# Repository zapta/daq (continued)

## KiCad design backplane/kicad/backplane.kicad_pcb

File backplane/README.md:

# Data Acquisition - Backplane

| :warning: WARNING                                               |
| :-------------------------------------------------------------- |
| This design is an unverified work in progress (as of May 2023). |

## Overview

The backplane is is a passive motherboard that accepts plugin boards with the functionality of the DAQ system.

## Design decisions

* Passive design, all active components are on plugin boards.
* Using common and inexpensive PCIE X8 connectors (98 pins). However, the power and signals are not compatible with PCIE.
* Symmetric slots. Slots are interchangeable and boards can be plugged in any slot. When applicable, conflict resolution is delegated to the plugin boards, e.g. using configuration jumpers.
* Scalable. Versions with higher/lower number of slots can be easily derived.
* 12-24VDC Power is provided via an on board connector and is routed to all slots. Plugin boards should use **insulated** DC/DC converters to generate supply rail voltages.
* Assigned pins for 5V supply, which is provided by an insulated power supply plugin board.
* Using through hole connectors for mechanical rigidity. An SMD version can be derived if so desired.
* 'Sufficient' signal integrity and bandwidth. The backplane is intended for relatively slow signals at the order of 1Mhz, that are driven directly by an MCU and peripherals, and thus, the backplane uses an inexpensive 4 layers PCB and minimal number of GND pins.

## Mechanical Dimensions

140mm X 67mm, 4 layers.

## Signals Assignment

As of May 2023, these are the assigned bus pins. All are reserved.

> **_TODO:_** Add the rest of the signals.

| Pin | Signal | Notes                            | Pin | Signal | Notes               |
| --- | ------ | -------------------------------- | --- | ------ | ------------------- |
| B1  | +5V    | Generated by Power Supply board. | A1  | GND    |                     |
| B2  | +5V    | Generated by Power Supply board. | A2  | GND    |                     |
| B3  | +5V    | Generated by Power Supply board. | A3  | GND    |                     |
| B4  | +5V    | Generated by Power Supply board. | A4  | GND    |                     |
| ... |        |                                  |     |        |                     |
| B48 | VIN+   | Insulated from GND. 12-24VDC     | A48 | VIN-   | Insulated from GND. |
| B49 | VIN+   | Insulated from GND. 12-24VDC     | A49 | VIN-   | Insulated from GND. |

## BOM

The key components are:

* PCIE X8 (98 pins) through hole connected. Preferably non slotted.
* JST XH two pin connector, preferably with positioning pin.

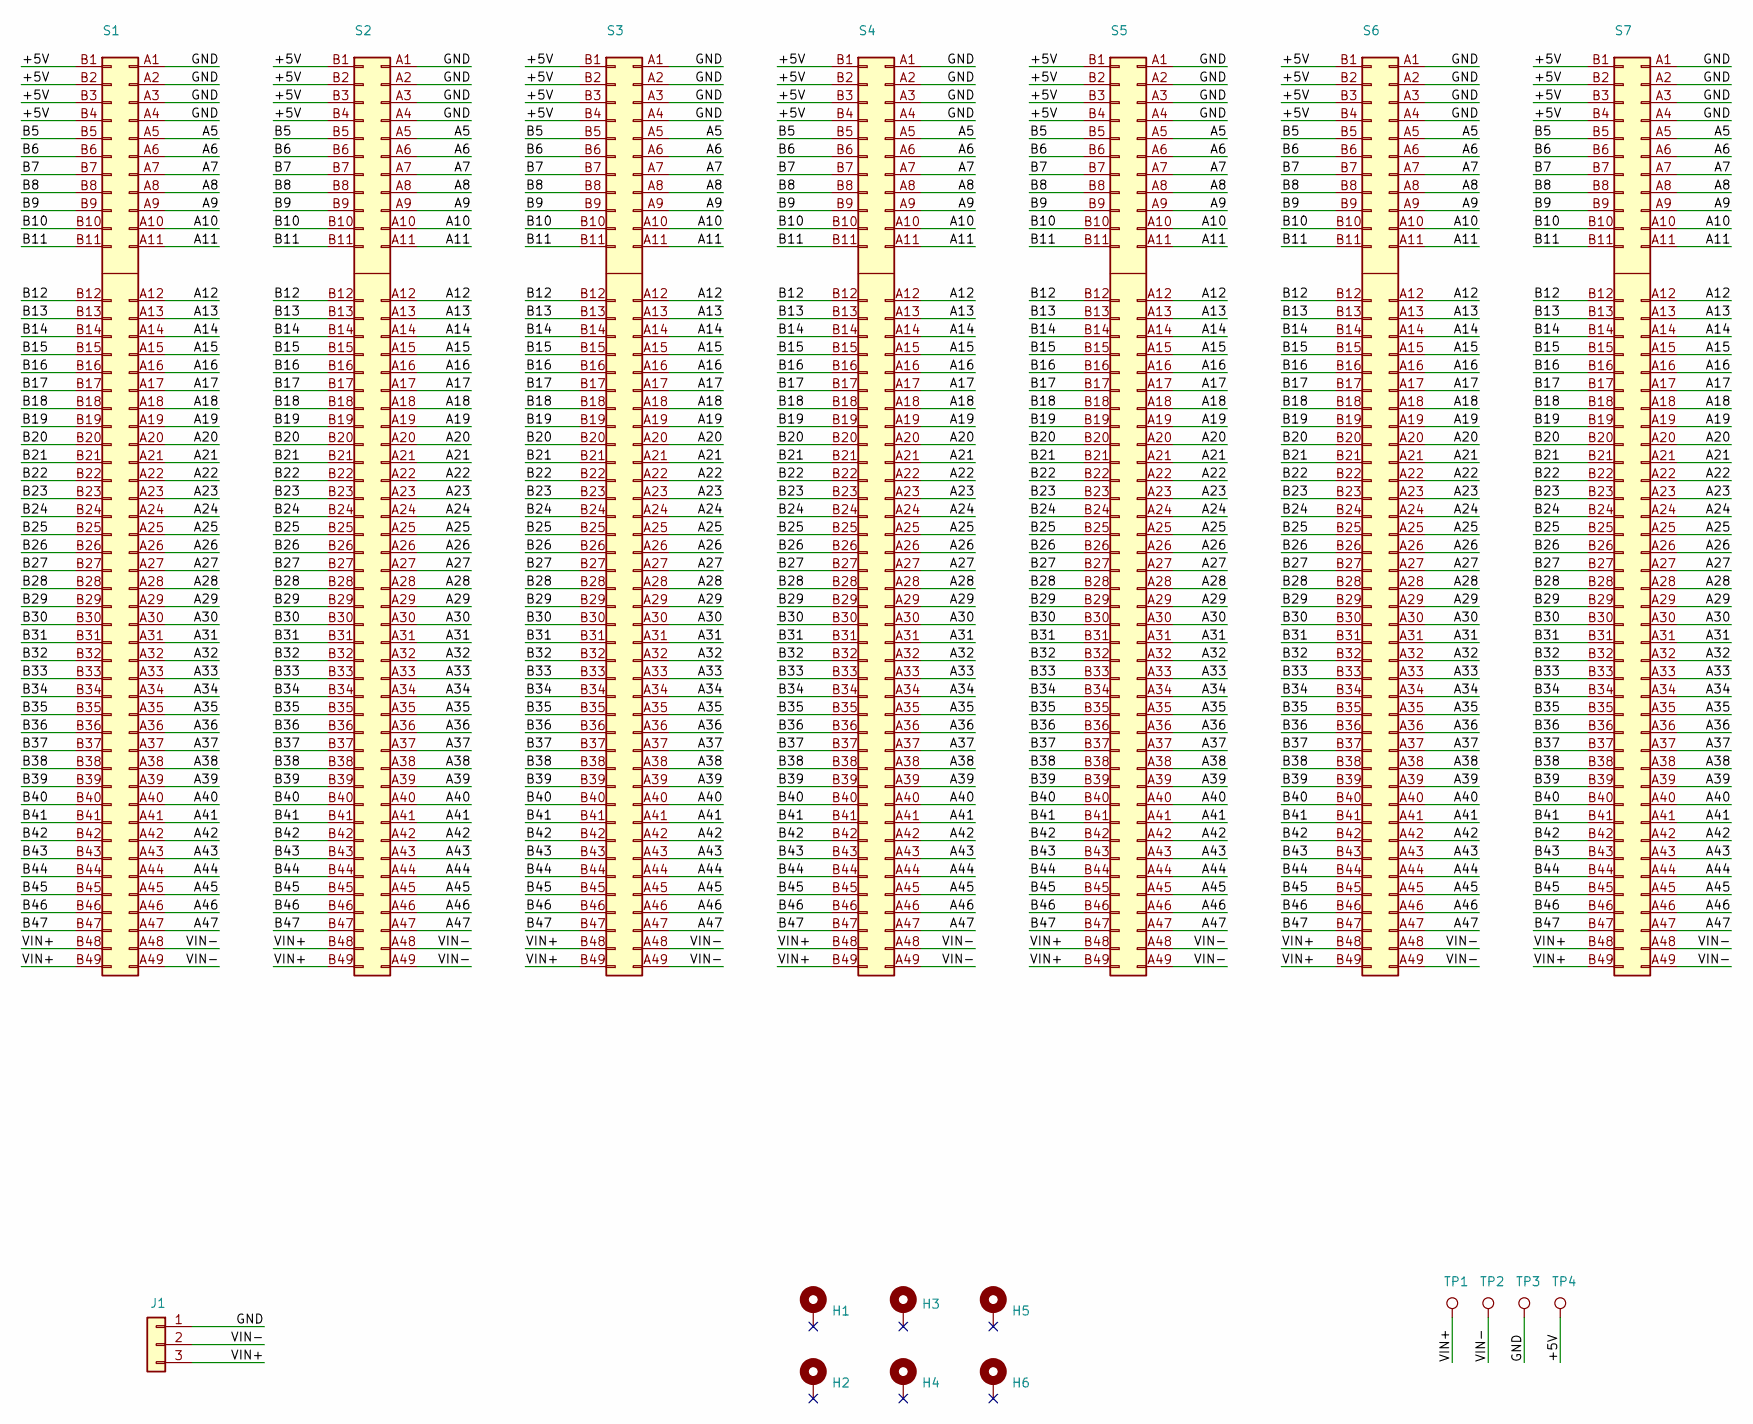
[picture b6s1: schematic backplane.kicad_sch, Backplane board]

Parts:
H1, H2, H3, H4, H5, H6: MountingHole; MountingHole_3.2mm_M3_Pad_Via
J1: Conn_01x02_Pin; TerminalBlock_3P_7.62mm; LCSC C557662
S1, S2, S3, S4, S5, S6, S7: pcie_98; pcie_98_socket
TP1, TP2, TP3, TP4: TestPoint; Test_Pad

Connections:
/+5V: S1.B1 (Pin_b1), S1.B2 (Pin_b2), S1.B3 (Pin_b3), S1.B4 (Pin_b4), S2.B1 (Pin_b1), S2.B2 (Pin_b2), S2.B3 (Pin_b3), S2.B4 (Pin_b4), S3.B1 (Pin_b1), S3.B2 (Pin_b2), S3.B3 (Pin_b3), S3.B4 (Pin_b4), S4.B1 (Pin_b1), S4.B2 (Pin_b2), S4.B3 (Pin_b3), S4.B4 (Pin_b4), S5.B1 (Pin_b1), S5.B2 (Pin_b2), S5.B3 (Pin_b3), S5.B4 (Pin_b4), S6.B1 (Pin_b1), S6.B2 (Pin_b2), S6.B3 (Pin_b3), S6.B4 (Pin_b4), S7.B1 (Pin_b1), S7.B2 (Pin_b2), S7.B3 (Pin_b3), S7.B4 (Pin_b4), TP4.1
/A5: S1.A5 (Pin_a5), S2.A5 (Pin_a5), S3.A5 (Pin_a5), S4.A5 (Pin_a5), S5.A5 (Pin_a5), S6.A5 (Pin_a5), S7.A5 (Pin_a5)
/A6: S1.A6 (Pin_a6), S2.A6 (Pin_a6), S3.A6 (Pin_a6), S4.A6 (Pin_a6), S5.A6 (Pin_a6), S6.A6 (Pin_a6), S7.A6 (Pin_a6)
/A7: S1.A7 (Pin_a7), S2.A7 (Pin_a7), S3.A7 (Pin_a7), S4.A7 (Pin_a7), S5.A7 (Pin_a7), S6.A7 (Pin_a7), S7.A7 (Pin_a7)
/A8: S1.A8 (Pin_a8), S2.A8 (Pin_a8), S3.A8 (Pin_a8), S4.A8 (Pin_a8), S5.A8 (Pin_a8), S6.A8 (Pin_a8), S7.A8 (Pin_a8)
/A9: S1.A9 (Pin_a9), S2.A9 (Pin_a9), S3.A9 (Pin_a9), S4.A9 (Pin_a9), S5.A9 (Pin_a9), S6.A9 (Pin_a9), S7.A9 (Pin_a9)
/A10: S1.A10 (Pin_a10), S2.A10 (Pin_a10), S3.A10 (Pin_a10), S4.A10 (Pin_a10), S5.A10 (Pin_a10), S6.A10 (Pin_a10), S7.A10 (Pin_a10)
/A11: S1.A11, S2.A11, S3.A11, S4.A11, S5.A11, S6.A11, S7.A11
/A12: S1.A12 (Pin_a12), S2.A12 (Pin_a12), S3.A12 (Pin_a12), S4.A12 (Pin_a12), S5.A12 (Pin_a12), S6.A12 (Pin_a12), S7.A12 (Pin_a12)
/A13: S1.A13 (Pin_a13), S2.A13 (Pin_a13), S3.A13 (Pin_a13), S4.A13 (Pin_a13), S5.A13 (Pin_a13), S6.A13 (Pin_a13), S7.A13 (Pin_a13)
/A14: S1.A14 (Pin_a14), S2.A14 (Pin_a14), S3.A14 (Pin_a14), S4.A14 (Pin_a14), S5.A14 (Pin_a14), S6.A14 (Pin_a14), S7.A14 (Pin_a14)
/A15: S1.A15 (Pin_a15), S2.A15 (Pin_a15), S3.A15 (Pin_a15), S4.A15 (Pin_a15), S5.A15 (Pin_a15), S6.A15 (Pin_a15), S7.A15 (Pin_a15)
/A16: S1.A16 (Pin_a16), S2.A16 (Pin_a16), S3.A16 (Pin_a16), S4.A16 (Pin_a16), S5.A16 (Pin_a16), S6.A16 (Pin_a16), S7.A16 (Pin_a16)
/A17: S1.A17 (Pin_a17), S2.A17 (Pin_a17), S3.A17 (Pin_a17), S4.A17 (Pin_a17), S5.A17 (Pin_a17), S6.A17 (Pin_a17), S7.A17 (Pin_a17)
/A18: S1.A18 (Pin_a18), S2.A18 (Pin_a18), S3.A18 (Pin_a18), S4.A18 (Pin_a18), S5.A18 (Pin_a18), S6.A18 (Pin_a18), S7.A18 (Pin_a18)
/A19: S1.A19 (Pin_a19), S2.A19 (Pin_a19), S3.A19 (Pin_a19), S4.A19 (Pin_a19), S5.A19 (Pin_a19), S6.A19 (Pin_a19), S7.A19 (Pin_a19)
/A20: S1.A20 (Pin_a20), S2.A20 (Pin_a20), S3.A20 (Pin_a20), S4.A20 (Pin_a20), S5.A20 (Pin_a20), S6.A20 (Pin_a20), S7.A20 (Pin_a20)
/A21: S1.A21 (Pin_a21), S2.A21 (Pin_a21), S3.A21 (Pin_a21), S4.A21 (Pin_a21), S5.A21 (Pin_a21), S6.A21 (Pin_a21), S7.A21 (Pin_a21)
/A22: S1.A22 (Pin_a22), S2.A22 (Pin_a22), S3.A22 (Pin_a22), S4.A22 (Pin_a22), S5.A22 (Pin_a22), S6.A22 (Pin_a22), S7.A22 (Pin_a22)
/A23: S1.A23 (Pin_a23), S2.A23 (Pin_a23), S3.A23 (Pin_a23), S4.A23 (Pin_a23), S5.A23 (Pin_a23), S6.A23 (Pin_a23), S7.A23 (Pin_a23)
/A24: S1.A24 (Pin_a24), S2.A24 (Pin_a24), S3.A24 (Pin_a24), S4.A24 (Pin_a24), S5.A24 (Pin_a24), S6.A24 (Pin_a24), S7.A24 (Pin_a24)
/A25: S1.A25 (Pin_a25), S2.A25 (Pin_a25), S3.A25 (Pin_a25), S4.A25 (Pin_a25), S5.A25 (Pin_a25), S6.A25 (Pin_a25), S7.A25 (Pin_a25)
/A26: S1.A26 (Pin_a26), S2.A26 (Pin_a26), S3.A26 (Pin_a26), S4.A26 (Pin_a26), S5.A26 (Pin_a26), S6.A26 (Pin_a26), S7.A26 (Pin_a26)
/A27: S1.A27 (Pin_a27), S2.A27 (Pin_a27), S3.A27 (Pin_a27), S4.A27 (Pin_a27), S5.A27 (Pin_a27), S6.A27 (Pin_a27), S7.A27 (Pin_a27)
/A28: S1.A28 (Pin_a28), S2.A28 (Pin_a28), S3.A28 (Pin_a28), S4.A28 (Pin_a28), S5.A28 (Pin_a28), S6.A28 (Pin_a28), S7.A28 (Pin_a28)
/A29: S1.A29 (Pin_a29), S2.A29 (Pin_a29), S3.A29 (Pin_a29), S4.A29 (Pin_a29), S5.A29 (Pin_a29), S6.A29 (Pin_a29), S7.A29 (Pin_a29)
/A30: S1.A30 (Pin_a30), S2.A30 (Pin_a30), S3.A30 (Pin_a30), S4.A30 (Pin_a30), S5.A30 (Pin_a30), S6.A30 (Pin_a30), S7.A30 (Pin_a30)
/A31: S1.A31 (Pin_a31), S2.A31 (Pin_a31), S3.A31 (Pin_a31), S4.A31 (Pin_a31), S5.A31 (Pin_a31), S6.A31 (Pin_a31), S7.A31 (Pin_a31)
/A32: S1.A32 (Pin_a32), S2.A32 (Pin_a32), S3.A32 (Pin_a32), S4.A32 (Pin_a32), S5.A32 (Pin_a32), S6.A32 (Pin_a32), S7.A32 (Pin_a32)
/A33: S1.A33 (Pin_a33), S2.A33 (Pin_a33), S3.A33 (Pin_a33), S4.A33 (Pin_a33), S5.A33 (Pin_a33), S6.A33 (Pin_a33), S7.A33 (Pin_a33)
/A34: S1.A34 (Pin_a34), S2.A34 (Pin_a34), S3.A34 (Pin_a34), S4.A34 (Pin_a34), S5.A34 (Pin_a34), S6.A34 (Pin_a34), S7.A34 (Pin_a34)
/A35: S1.A35 (Pin_a35), S2.A35 (Pin_a35), S3.A35 (Pin_a35), S4.A35 (Pin_a35), S5.A35 (Pin_a35), S6.A35 (Pin_a35), S7.A35 (Pin_a35)
/A36: S1.A36 (Pin_a36), S2.A36 (Pin_a36), S3.A36 (Pin_a36), S4.A36 (Pin_a36), S5.A36 (Pin_a36), S6.A36 (Pin_a36), S7.A36 (Pin_a36)
/A37: S1.A37 (Pin_a37), S2.A37 (Pin_a37), S3.A37 (Pin_a37), S4.A37 (Pin_a37), S5.A37 (Pin_a37), S6.A37 (Pin_a37), S7.A37 (Pin_a37)
/A38: S1.A38 (Pin_a38), S2.A38 (Pin_a38), S3.A38 (Pin_a38), S4.A38 (Pin_a38), S5.A38 (Pin_a38), S6.A38 (Pin_a38), S7.A38 (Pin_a38)
/A39: S1.A39 (Pin_a39), S2.A39 (Pin_a39), S3.A39 (Pin_a39), S4.A39 (Pin_a39), S5.A39 (Pin_a39), S6.A39 (Pin_a39), S7.A39 (Pin_a39)
/A40: S1.A40 (Pin_a40), S2.A40 (Pin_a40), S3.A40 (Pin_a40), S4.A40 (Pin_a40), S5.A40 (Pin_a40), S6.A40 (Pin_a40), S7.A40 (Pin_a40)
/A41: S1.A41 (Pin_a41), S2.A41 (Pin_a41), S3.A41 (Pin_a41), S4.A41 (Pin_a41), S5.A41 (Pin_a41), S6.A41 (Pin_a41), S7.A41 (Pin_a41)
/A42: S1.A42 (Pin_a42), S2.A42 (Pin_a42), S3.A42 (Pin_a42), S4.A42 (Pin_a42), S5.A42 (Pin_a42), S6.A42 (Pin_a42), S7.A42 (Pin_a42)
/A43: S1.A43 (Pin_a43), S2.A43 (Pin_a43), S3.A43 (Pin_a43), S4.A43 (Pin_a43), S5.A43 (Pin_a43), S6.A43 (Pin_a43), S7.A43 (Pin_a43)
/A44: S1.A44 (Pin_a44), S2.A44 (Pin_a44), S3.A44 (Pin_a44), S4.A44 (Pin_a44), S5.A44 (Pin_a44), S6.A44 (Pin_a44), S7.A44 (Pin_a44)
/A45: S1.A45 (Pin_a45), S2.A45 (Pin_a45), S3.A45 (Pin_a45), S4.A45 (Pin_a45), S5.A45 (Pin_a45), S6.A45 (Pin_a45), S7.A45 (Pin_a45)
/A46: S1.A46 (Pin_a46), S2.A46 (Pin_a46), S3.A46 (Pin_a46), S4.A46 (Pin_a46), S5.A46 (Pin_a46), S6.A46 (Pin_a46), S7.A46 (Pin_a46)
/A47: S1.A47 (Pin_a47), S2.A47 (Pin_a47), S3.A47 (Pin_a47), S4.A47 (Pin_a47), S5.A47 (Pin_a47), S6.A47 (Pin_a47), S7.A47 (Pin_a47)
/B5: S1.B5 (Pin_b5), S2.B5 (Pin_b5), S3.B5 (Pin_b5), S4.B5 (Pin_b5), S5.B5 (Pin_b5), S6.B5 (Pin_b5), S7.B5 (Pin_b5)
/B6: S1.B6 (Pin_b6), S2.B6 (Pin_b6), S3.B6 (Pin_b6), S4.B6 (Pin_b6), S5.B6 (Pin_b6), S6.B6 (Pin_b6), S7.B6 (Pin_b6)
/B7: S1.B7 (Pin_b7), S2.B7 (Pin_b7), S3.B7 (Pin_b7), S4.B7 (Pin_b7), S5.B7 (Pin_b7), S6.B7 (Pin_b7), S7.B7 (Pin_b7)
/B8: S1.B8 (Pin_b8), S2.B8 (Pin_b8), S3.B8 (Pin_b8), S4.B8 (Pin_b8), S5.B8 (Pin_b8), S6.B8 (Pin_b8), S7.B8 (Pin_b8)
/B9: S1.B9 (Pin_b9), S2.B9 (Pin_b9), S3.B9 (Pin_b9), S4.B9 (Pin_b9), S5.B9 (Pin_b9), S6.B9 (Pin_b9), S7.B9 (Pin_b9)
/B10: S1.B10 (Pin_b10), S2.B10 (Pin_b10), S3.B10 (Pin_b10), S4.B10 (Pin_b10), S5.B10 (Pin_b10), S6.B10 (Pin_b10), S7.B10 (Pin_b10)
/B11: S1.B11 (Pin_b11), S2.B11 (Pin_b11), S3.B11 (Pin_b11), S4.B11 (Pin_b11), S5.B11 (Pin_b11), S6.B11 (Pin_b11), S7.B11 (Pin_b11)
/B12: S1.B12 (Pin_b12), S2.B12 (Pin_b12), S3.B12 (Pin_b12), S4.B12 (Pin_b12), S5.B12 (Pin_b12), S6.B12 (Pin_b12), S7.B12 (Pin_b12)
/B13: S1.B13 (Pin_b13), S2.B13 (Pin_b13), S3.B13 (Pin_b13), S4.B13 (Pin_b13), S5.B13 (Pin_b13), S6.B13 (Pin_b13), S7.B13 (Pin_b13)
/B14: S1.B14 (Pin_b14), S2.B14 (Pin_b14), S3.B14 (Pin_b14), S4.B14 (Pin_b14), S5.B14 (Pin_b14), S6.B14 (Pin_b14), S7.B14 (Pin_b14)
/B15: S1.B15 (Pin_b15), S2.B15 (Pin_b15), S3.B15 (Pin_b15), S4.B15 (Pin_b15), S5.B15 (Pin_b15), S6.B15 (Pin_b15), S7.B15 (Pin_b15)
/B16: S1.B16 (Pin_b16), S2.B16 (Pin_b16), S3.B16 (Pin_b16), S4.B16 (Pin_b16), S5.B16 (Pin_b16), S6.B16 (Pin_b16), S7.B16 (Pin_b16)
/B17: S1.B17 (Pin_b17), S2.B17 (Pin_b17), S3.B17 (Pin_b17), S4.B17 (Pin_b17), S5.B17 (Pin_b17), S6.B17 (Pin_b17), S7.B17 (Pin_b17)
/B18: S1.B18 (Pin_b18), S2.B18 (Pin_b18), S3.B18 (Pin_b18), S4.B18 (Pin_b18), S5.B18 (Pin_b18), S6.B18 (Pin_b18), S7.B18 (Pin_b18)
/B19: S1.B19 (Pin_b19), S2.B19 (Pin_b19), S3.B19 (Pin_b19), S4.B19 (Pin_b19), S5.B19 (Pin_b19), S6.B19 (Pin_b19), S7.B19 (Pin_b19)
/B20: S1.B20 (Pin_b20), S2.B20 (Pin_b20), S3.B20 (Pin_b20), S4.B20 (Pin_b20), S5.B20 (Pin_b20), S6.B20 (Pin_b20), S7.B20 (Pin_b20)
/B21: S1.B21 (Pin_b21), S2.B21 (Pin_b21), S3.B21 (Pin_b21), S4.B21 (Pin_b21), S5.B21 (Pin_b21), S6.B21 (Pin_b21), S7.B21 (Pin_b21)
/B22: S1.B22 (Pin_b22), S2.B22 (Pin_b22), S3.B22 (Pin_b22), S4.B22 (Pin_b22), S5.B22 (Pin_b22), S6.B22 (Pin_b22), S7.B22 (Pin_b22)
/B23: S1.B23 (Pin_b23), S2.B23 (Pin_b23), S3.B23 (Pin_b23), S4.B23 (Pin_b23), S5.B23 (Pin_b23), S6.B23 (Pin_b23), S7.B23 (Pin_b23)
/B24: S1.B24 (Pin_b24), S2.B24 (Pin_b24), S3.B24 (Pin_b24), S4.B24 (Pin_b24), S5.B24 (Pin_b24), S6.B24 (Pin_b24), S7.B24 (Pin_b24)
/B25: S1.B25 (Pin_b25), S2.B25 (Pin_b25), S3.B25 (Pin_b25), S4.B25 (Pin_b25), S5.B25 (Pin_b25), S6.B25 (Pin_b25), S7.B25 (Pin_b25)
/B26: S1.B26 (Pin_b26), S2.B26 (Pin_b26), S3.B26 (Pin_b26), S4.B26 (Pin_b26), S5.B26 (Pin_b26), S6.B26 (Pin_b26), S7.B26 (Pin_b26)
/B27: S1.B27 (Pin_b27), S2.B27 (Pin_b27), S3.B27 (Pin_b27), S4.B27 (Pin_b27), S5.B27 (Pin_b27), S6.B27 (Pin_b27), S7.B27 (Pin_b27)
/B28: S1.B28 (Pin_b28), S2.B28 (Pin_b28), S3.B28 (Pin_b28), S4.B28 (Pin_b28), S5.B28 (Pin_b28), S6.B28 (Pin_b28), S7.B28 (Pin_b28)
/B29: S1.B29 (Pin_b29), S2.B29 (Pin_b29), S3.B29 (Pin_b29), S4.B29 (Pin_b29), S5.B29 (Pin_b29), S6.B29 (Pin_b29), S7.B29 (Pin_b29)
/B30: S1.B30 (Pin_b30), S2.B30 (Pin_b30), S3.B30 (Pin_b30), S4.B30 (Pin_b30), S5.B30 (Pin_b30), S6.B30 (Pin_b30), S7.B30 (Pin_b30)
/B31: S1.B31 (Pin_b31), S2.B31 (Pin_b31), S3.B31 (Pin_b31), S4.B31 (Pin_b31), S5.B31 (Pin_b31), S6.B31 (Pin_b31), S7.B31 (Pin_b31)
/B32: S1.B32 (Pin_b32), S2.B32 (Pin_b32), S3.B32 (Pin_b32), S4.B32 (Pin_b32), S5.B32 (Pin_b32), S6.B32 (Pin_b32), S7.B32 (Pin_b32)
/B33: S1.B33 (Pin_b33), S2.B33 (Pin_b33), S3.B33 (Pin_b33), S4.B33 (Pin_b33), S5.B33 (Pin_b33), S6.B33 (Pin_b33), S7.B33 (Pin_b33)
/B34: S1.B34 (Pin_b34), S2.B34 (Pin_b34), S3.B34 (Pin_b34), S4.B34 (Pin_b34), S5.B34 (Pin_b34), S6.B34 (Pin_b34), S7.B34 (Pin_b34)
/B35: S1.B35 (Pin_b35), S2.B35 (Pin_b35), S3.B35 (Pin_b35), S4.B35 (Pin_b35), S5.B35 (Pin_b35), S6.B35 (Pin_b35), S7.B35 (Pin_b35)
/B36: S1.B36 (Pin_b36), S2.B36 (Pin_b36), S3.B36 (Pin_b36), S4.B36 (Pin_b36), S5.B36 (Pin_b36), S6.B36 (Pin_b36), S7.B36 (Pin_b36)
/B37: S1.B37 (Pin_b37), S2.B37 (Pin_b37), S3.B37 (Pin_b37), S4.B37 (Pin_b37), S5.B37 (Pin_b37), S6.B37 (Pin_b37), S7.B37 (Pin_b37)
/B38: S1.B38 (Pin_b38), S2.B38 (Pin_b38), S3.B38 (Pin_b38), S4.B38 (Pin_b38), S5.B38 (Pin_b38), S6.B38 (Pin_b38), S7.B38 (Pin_b38)
/B39: S1.B39 (Pin_b39), S2.B39 (Pin_b39), S3.B39 (Pin_b39), S4.B39 (Pin_b39), S5.B39 (Pin_b39), S6.B39 (Pin_b39), S7.B39 (Pin_b39)
/B40: S1.B40 (Pin_b40), S2.B40 (Pin_b40), S3.B40 (Pin_b40), S4.B40 (Pin_b40), S5.B40 (Pin_b40), S6.B40 (Pin_b40), S7.B40 (Pin_b40)
/B41: S1.B41 (Pin_b41), S2.B41 (Pin_b41), S3.B41 (Pin_b41), S4.B41 (Pin_b41), S5.B41 (Pin_b41), S6.B41 (Pin_b41), S7.B41 (Pin_b41)
/B42: S1.B42 (Pin_b42), S2.B42 (Pin_b42), S3.B42 (Pin_b42), S4.B42 (Pin_b42), S5.B42 (Pin_b42), S6.B42 (Pin_b42), S7.B42 (Pin_b42)
/B43: S1.B43 (Pin_b43), S2.B43 (Pin_b43), S3.B43 (Pin_b43), S4.B43 (Pin_b43), S5.B43 (Pin_b43), S6.B43 (Pin_b43), S7.B43 (Pin_b43)
/B44: S1.B44 (Pin_b44), S2.B44 (Pin_b44), S3.B44 (Pin_b44), S4.B44 (Pin_b44), S5.B44 (Pin_b44), S6.B44 (Pin_b44), S7.B44 (Pin_b44)
/B45: S1.B45 (Pin_b45), S2.B45 (Pin_b45), S3.B45 (Pin_b45), S4.B45 (Pin_b45), S5.B45 (Pin_b45), S6.B45 (Pin_b45), S7.B45 (Pin_b45)
/B46: S1.B46 (Pin_46), S2.B46 (Pin_46), S3.B46 (Pin_46), S4.B46 (Pin_46), S5.B46 (Pin_46), S6.B46 (Pin_46), S7.B46 (Pin_46)
/B47: S1.B47 (Pin_b47), S2.B47 (Pin_b47), S3.B47 (Pin_b47), S4.B47 (Pin_b47), S5.B47 (Pin_b47), S6.B47 (Pin_b47), S7.B47 (Pin_b47)
/GND: J1.1, S1.A1 (Pin_a1), S1.A2 (Pin_a2), S1.A3 (Pin_a3), S1.A4 (Pin_a4), S2.A1 (Pin_a1), S2.A2 (Pin_a2), S2.A3 (Pin_a3), S2.A4 (Pin_a4), S3.A1 (Pin_a1), S3.A2 (Pin_a2), S3.A3 (Pin_a3), S3.A4 (Pin_a4), S4.A1 (Pin_a1), S4.A2 (Pin_a2), S4.A3 (Pin_a3), S4.A4 (Pin_a4), S5.A1 (Pin_a1), S5.A2 (Pin_a2), S5.A3 (Pin_a3), S5.A4 (Pin_a4), S6.A1 (Pin_a1), S6.A2 (Pin_a2), S6.A3 (Pin_a3), S6.A4 (Pin_a4), S7.A1 (Pin_a1), S7.A2 (Pin_a2), S7.A3 (Pin_a3), S7.A4 (Pin_a4), TP3.1
/VIN+: J1.3, S1.B48 (Pin_b48), S1.B49 (Pin_b49), S2.B48 (Pin_b48), S2.B49 (Pin_b49), S3.B48 (Pin_b48), S3.B49 (Pin_b49), S4.B48 (Pin_b48), S4.B49 (Pin_b49), S5.B48 (Pin_b48), S5.B49 (Pin_b49), S6.B48 (Pin_b48), S6.B49 (Pin_b49), S7.B48 (Pin_b48), S7.B49 (Pin_b49), TP1.1
/VIN-: J1.2, S1.A48 (Pin_a48), S1.A49 (Pin_a49), S2.A48 (Pin_a48), S2.A49 (Pin_a49), S3.A48 (Pin_a48), S3.A49 (Pin_a49), S4.A48 (Pin_a48), S4.A49 (Pin_a49), S5.A48 (Pin_a48), S5.A49 (Pin_a49), S6.A48 (Pin_a48), S6.A49 (Pin_a49), S7.A48 (Pin_a48), S7.A49 (Pin_a49), TP2.1

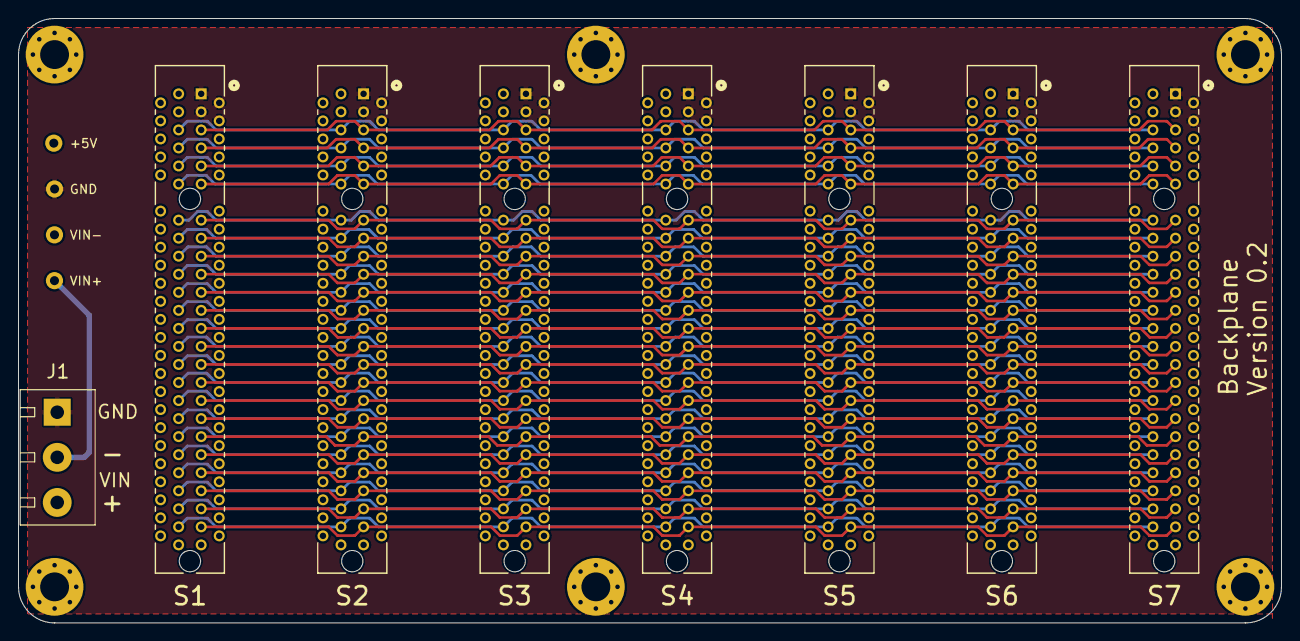
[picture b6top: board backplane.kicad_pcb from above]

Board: 4 copper layers, 140.0 x 67.0 mm, 18 parts (0 on the bottom side), 90 nets.

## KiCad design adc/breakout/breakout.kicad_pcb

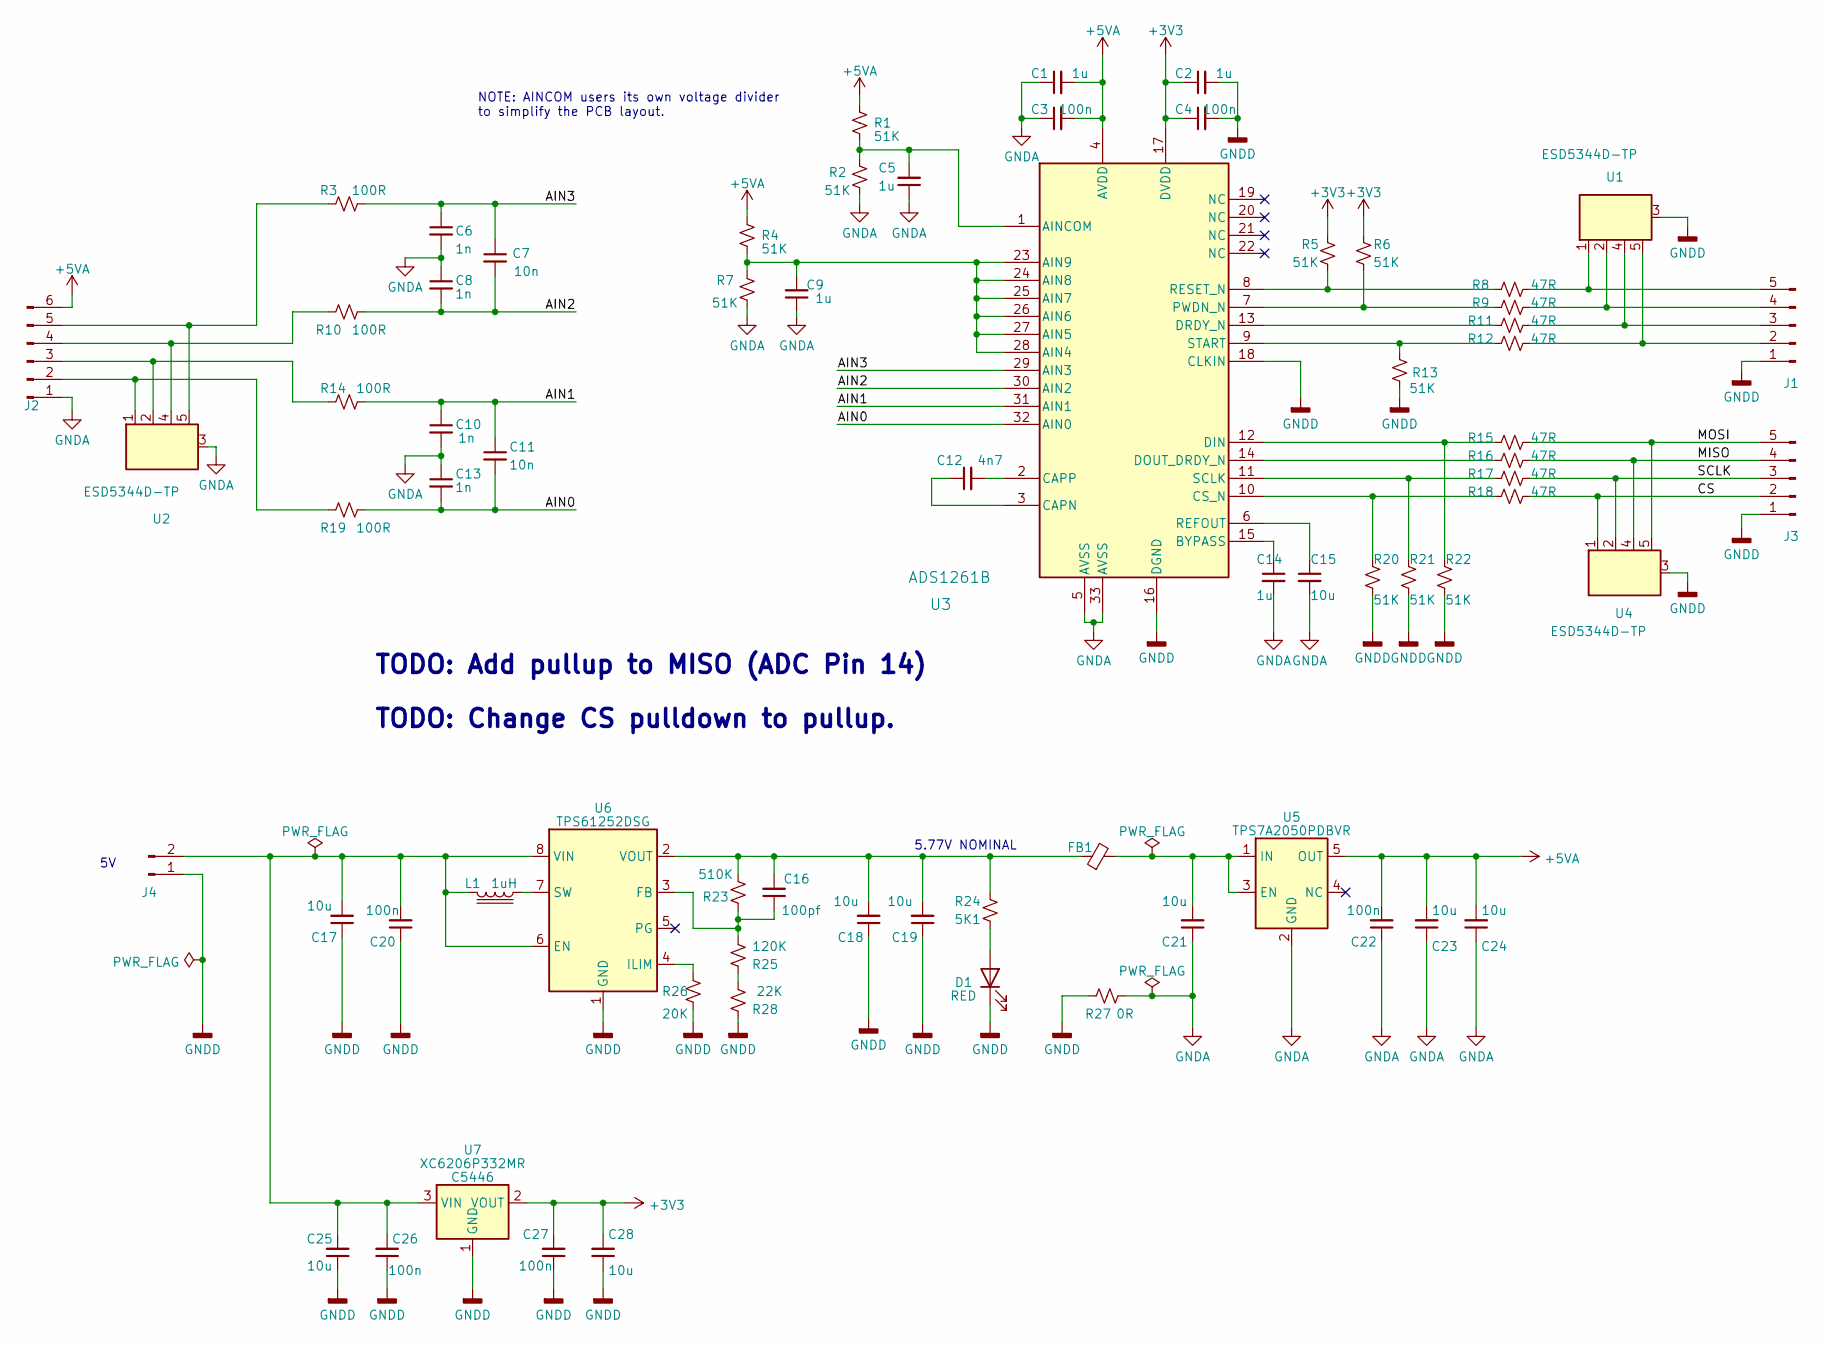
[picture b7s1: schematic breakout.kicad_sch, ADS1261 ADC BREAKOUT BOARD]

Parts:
C1, C2, C5, C9, C14: 1u; C_0402_1005Metric; LCSC C52923
C3, C4, C20, C22, C26, C27: 100n; C_0402_1005Metric; LCSC C1525
C6, C8, C10, C13: 1n; C_0402_1005Metric; LCSC C1523
C7, C11: 10n; C_0402_1005Metric; LCSC C15195
C12: 4n7; C_0402_1005Metric; LCSC C1538
C15, C17, C18, C19, C21, C23, C24, C25, C28: 10u; C_0603_1608Metric; LCSC C96446
C16: 100pf; C_0402_1005Metric; LCSC C1546
D1: RED; LED_0805_2012Metric; LCSC C84256
FB1: Ferrite Bead; L_0805_2012Metric; LCSC C1017
J1, J3: Conn_01x05_Pin; PinHeader_1x05_P2.54mm_Vertical; LCSC DNP
J2: Conn_01x06_Pin; PinHeader_1x06_P2.54mm_Vertical; LCSC DNP
J4: Conn_01x03_Pin; PinHeader_1x02_P2.54mm_Vertical; LCSC DNP
L1: 1uH; L_1210_3225Metric; LCSC C703782
R1, R2, R4, R5, R6, R7, R13, R20, R21, R22: 51K; R_0402_1005Metric; LCSC C25794
R3, R10, R14, R19: 100R; R_0402_1005Metric; LCSC C25076
R8, R9, R11, R12, R15, R16, R17, R18: 47R; R_0402_1005Metric; LCSC C25118
R23: 510K; R_0402_1005Metric; LCSC C11616
R24: 5K1; R_0402_1005Metric; LCSC C25905
R25: 120K; R_0402_1005Metric; LCSC C25750
R26: 20K; R_0402_1005Metric; LCSC C25765
R27: 0R; R_0805_2012Metric; LCSC C17477
R28: 22K; R_0402_1005Metric; LCSC C25768
U1, U2, U4: ESD5344D-TP; Diodes_UDFN-10_1.0x2.5mm_P0.5mm; LCSC C2841840
U3: ADS1261B; RHB0032E; LCSC DNP
U5: TPS7A2050PDBVR; SOT-23-5; LCSC DNP
U6: TPS61252DSG; WSON-8-1EP_2x2mm_P0.5mm_EP0.9x1.6mm; LCSC C128617
U7: XC6206P332MR; SOT-23-3; LCSC C5446

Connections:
+3V3: C2.1, C4.1, C27.2, C28.2, R5.2, R6.2, U3.17 (DVDD), U7.2 (VOUT)
+5VA: C1.2, C3.2, C22.2, C23.2, C24.2, J2.6, R1.2, R4.2, U3.4 (AVDD), U5.5 (OUT)
/AIN0: C11.2, C13.2, R19.2, U3.32 (AIN0)
/AIN1: C10.1, C11.1, R14.2, U3.31 (AIN1)
/AIN2: C7.2, C8.2, R10.2, U3.30 (AIN2)
/AIN3: C6.1, C7.1, R3.2, U3.29 (AIN3)
/CS: J3.2, R18.1, U4.1 (D1)
/MISO: J3.4, R16.1, U4.4 (D3)
/MOSI: J3.5, R15.1, U4.5 (D4)
/SCLK: J3.3, R17.1, U4.2 (D2)
GNDA: C1.1, C3.1, C5.1, C6.2, C8.1, C9.1, C10.2, C13.1, C14.2, C15.2, C21.1, C22.1, C23.1, C24.1, J2.1, R2.1, R7.1, R27.2, U2.3 (GND), U3.5 (AVSS), U3.33 (AVSS), U5.2 (GND)
GNDD: C2.2, C4.2, C17.1, C18.1, C19.1, C20.1, C25.1, C26.1, C27.1, C28.1, D1.1 (K), J1.1, J3.1, J4.1, R13.1, R20.1, R21.1, R22.1, R26.2, R27.1, R28.1, U1.3 (GND), U3.16 (DGND), U3.18 (CLKIN), U4.3 (GND), U6.1 (GND), U6.9 (GND), U7.1 (GND)
unnamed: D1.2 (A), R24.2
unnamed: J1.2, R12.1, U1.5 (D4)
unnamed: J1.3, R11.1, U1.4 (D3)
unnamed: J1.4, R9.1, U1.2 (D2)
unnamed: J1.5, R8.1, U1.1 (D1)
unnamed: J2.2, R19.1, U2.1 (D1)
unnamed: J2.3, R14.1, U2.2 (D2)
unnamed: J2.4, R10.1, U2.4 (D3)
unnamed: J2.5, R3.1, U2.5 (D4)
unnamed: C17.2, C20.2, C25.2, C26.2, J4.2, L1.1, U6.6 (EN), U6.8 (VIN), U7.3 (VIN)
unnamed: R25.1, R28.2
unnamed: C9.2, R4.1, R7.2, U3.23 (AIN9), U3.24 (AIN8), U3.25 (AIN7), U3.26 (AIN6), U3.27 (AIN5), U3.28 (AIN4)
unnamed: C5.2, R1.1, R2.2, U3.1 (AINCOM)
unnamed: C14.1, U3.15 (BYPASS)
unnamed: C12.1, U3.3 (CAPN)
unnamed: C12.2, U3.2 (CAPP)
unnamed: R18.2, R20.2, U3.10 (CS_N)
unnamed: R15.2, R22.2, U3.12 (DIN)
unnamed: R16.2, U3.14 (DOUT_DRDY_N)
unnamed: R11.2, U3.13 (DRDY_N)
unnamed: R6.1, R9.2, U3.7 (PWDN_N)
unnamed: C15.1, U3.6 (REFOUT)
unnamed: R5.1, R8.2, U3.8 (RESET_N)
unnamed: R17.2, R21.2, U3.11 (SCLK)
unnamed: R12.2, R13.2, U3.9 (START)
unnamed: C21.2, FB1.2, U5.1 (IN), U5.3 (EN)
unnamed: C16.1, R23.2, R25.2, U6.3 (FB)
unnamed: R26.1, U6.4 (ILIM)
unnamed: L1.2, U6.7 (SW)
unnamed: C16.2, C18.2, C19.2, FB1.1, R23.1, R24.1, U6.2 (VOUT)

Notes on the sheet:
TODO: Add pullup to MISO (ADC Pin 14)
NOTE: AINCOM users its own voltage divider to simplify the PCB layout.
TODO: Change CS pulldown to pullup.
5.77V NOMINAL

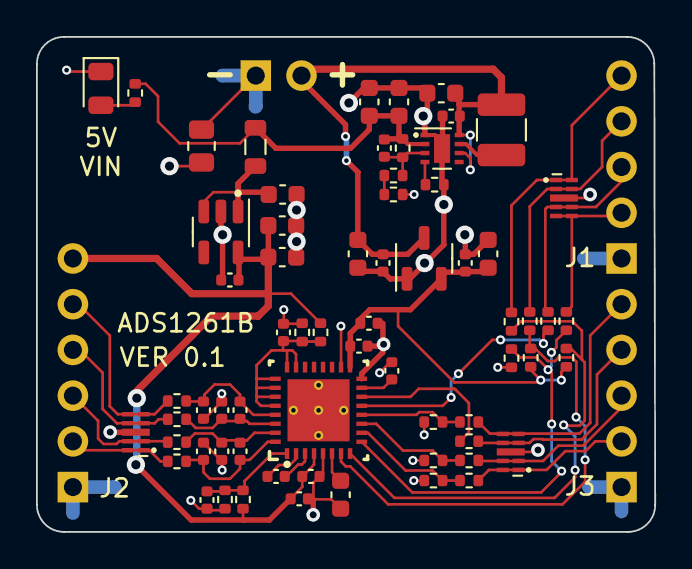
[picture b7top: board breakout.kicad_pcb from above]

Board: 2 copper layers, 34.4 x 27.5 mm, 70 parts (0 on the bottom side), 42 nets.

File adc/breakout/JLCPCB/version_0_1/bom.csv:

Designator,Footprint,Quantity,Value,LCSC Part #
"C1, C14, C2, C5, C9",0402,5,1u,C52923
"C10, C13, C6, C8",0402,4,1n,C1523
"C11, C7",0402,2,10n,C15195
C12,0402,1,4n7,C1538
"C15, C17, C18, C19, C21, C23, C24, C25, C28",0603,9,10u,C96446
C16,0402,1,100pf,C1546
"C20, C22, C26, C27, C3, C4",0402,6,100n,C1525
D1,0805,1,RED,C84256
FB1,0805,1,Ferrite Bead,C1017
"J1, J3",PinHeader_1x05_P2.54mm_Vertical,2,Conn_01x05_Pin,DNP
J2,PinHeader_1x06_P2.54mm_Vertical,1,Conn_01x06_Pin,DNP
J4,PinHeader_1x02_P2.54mm_Vertical,1,Conn_01x03_Pin,DNP
L1,1210,1,1uH,C703782
"R1, R13, R2, R20, R21, R22, R4, R5, R6, R7",0402,10,51K,C25794
"R10, R14, R19, R3",0402,4,100R,C25076
"R11, R12, R15, R16, R17, R18, R8, R9",0402,8,47R,C25118
R23,0402,1,510K,C11616
R24,0402,1,5K1,C25905
R25,0402,1,120K,C25750
R26,0402,1,20K,C25765
R27,0805,1,0R,C17477
R28,0402,1,22K,C25768
"U1, U2, U4",Diodes_UDFN-10_1.0x2.5mm_P0.5mm,3,ESD5344D-TP,C2841840
U3,RHB0032E,1,ADS1261B,DNP
U5,SOT-23-5,1,TPS7A2050PDBVR,DNP
U6,WSON-8-1EP_2x2mm_P0.5mm_EP0.9x1.6mm,1,TPS61252DSG,C128617
U7,SOT-23-3,1,XC6206P332MR,C5446

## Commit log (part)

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2023-07-18 Updated gitignore.
2023-07-19 Cleaned up TODOs for next version of backplane.
2023-07-20 Updated TODOs.
2023-07-20 Minor tweak of the schematics.
2023-07-22 Cleaned up the monitoring of thermistor 1 (added averaging)
2023-07-23 Updated the thermistor inputs to use 2K voltage divider.
2023-07-23 Removed the fork of the controller's kicad directory.
2023-07-23 Tweaked the ADC to reduce cross talk between the thermistor and load cell channels. Performing double conversion and selecting only the second value, PGA is always enabled. Works but not perfect. Ide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
2023-07-23 Added to the controller board text to remove D10.
2023-07-24 Added computation of thermistor temperature.
2023-07-24 Removed unused file.
2023-07-24 Added support for multiple thermistor graphs.
2023-07-24 Tweaked the monitor's graph legends.
2023-07-25 Abstracted monitor's load cell and thermistor channels.
2023-07-26 Removed obsolete production files.
2023-07-26 Renamed the fork of kicad adc to 'io'.
2023-07-26 IO board schematic in progress.
2023-07-27 IO board schematic is feature complete.
2023-07-27 Work in progress. Placement of the IO board.
2023-07-27 IO layout passes DRC.
2023-07-27 Tweaked IO board layout.
2023-07-27 Tweaked the IO card layout
2023-07-27 Locked UART2 and I/O pins in cube_ide. No semantic changed.
2023-07-27 Fixed the dimensions of the DC/DC footprint and generated production files.
2023-07-27 Fixed the part numbers and footpring of the IO board's 3.3V regulators.
2023-07-28 Updated LCSC parts numbers of ADC board.
2023-07-28 Added experimental directory.
2023-07-29 added to sys_config thermistor calibration table
2023-07-30 Calibrated the three thermistor channels.
2023-07-30 Added a second serial port. Will be used for printer link.
2023-07-30 Moved the declaration of the host link message and command handlers to the controller.
2023-07-30 Added to the controller the notion of an event.
2023-08-01 Changed serial rx to event driven mode, waiting on a binary semaphore rather than polling.
2023-08-01 Deleted the openocd debugger patch binary. Not needed anymore.
2023-08-01 Removed blank lines.
2023-08-01 Extended the StaticString class and optimized len().
2023-08-01 Implemented the printer link. Not tested yet.
2023-08-01 Device now report markers to recorder and to monitor.
2023-08-02 Added parsing of log markers.
2023-08-02 Deleted temporary files.
2023-08-03 Implemented monitor markers.
2023-08-03 Log processor now handles markers.
2023-08-03 Added a comment.
2023-08-04 Fixed the recording of short packets such as marker packet.
2023-08-04 Improve the monitor's reset detection by using the device session id.
2023-08-04 Updated the TODOs.
2023-08-04 Tweaked the marker pend specification.
2023-08-04 Reduced the thermistor graph x span from 200 secs to 70 secs.
2023-08-04 Added a skeleton of test collector program.
2023-08-05 Moved the marker configuration to sys_config.
2023-08-05 Make the marker configuration more flexible.
2023-08-05 Simplified the markers configurations.
2023-08-05 Tweked sys_config
2023-08-05 Changed the log processor to emit time as ints (millis), was float (secs).
2023-08-05 Minor progress on the test splitter.
2023-08-05 Renamed the test collector to test splitter.
2023-08-05 Test splitter works
2023-08-05 Renamed test begin/end markers.
2023-08-05 Refactored and cleanup the log processor and test splitter.
2023-08-05 Cleaned up data classes.
2023-08-05 Updated TODOs
2023-08-06 Make the serial initialization less sensitive to transient errors.
2023-08-06 Removed a too strict error check in the static binary semaphore.
2023-08-06 Improved debugging setting of error handler.
2023-08-06 Updated comments in platformio.ini
2023-08-07 Applied pathces to make the SD card detection and reinitialization to work.
2023-08-07 Monitor now shows indication of SD presence.
2023-08-07 Formatted data_recorder.cpp. No code change.
2023-08-07 Updated TODO
2023-08-07 Added to thermistors and RTD configurations an offset setting.
2023-08-07 Reenabled temp channel 3.
2023-08-07 Reformatted data_recorded.cpp
2023-08-08 Added forced deinitialization of the SD card reader.
2023-08-08 Updated git ignore.
2023-08-09 Changed the serial ports to use DMA.
2023-08-09 Added a trivial test.
2023-08-10 Commented out temp channel 3.
2023-08-10 Added host python requirements file.
2023-08-12 Fixed a display points leak.
2023-08-12 Improved the error recovery of serial rx.
2023-08-13 Fixed a typo.
2023-08-13 Deleted a temporary file
2023-08-13 Fixed the RTD R to C function.
2023-08-13 Updated sys config for the new controller's com port.
2023-08-14 Added TODOs to Kicad schematics.
2023-08-15 Added TODOs to kicad schematics (adding a serial number silkscreen)
2023-08-15 Changed default com port.
2023-08-15 Changed the RTD conversion formula.
2023-08-15 Removed references to UliEngineering. Not used anymore.
2023-08-16 Fixed the RTD conversion formula.
2023-08-16 Reformatted monitor.py
2023-08-17 Cleaned up python warnings in the monitor code.
2023-08-17 Added to the monitor experimental low pass filter.
2023-08-17 Fixed the RTD temperature interpolation algorithm.
2023-08-17 Added a unit test for the RTD R to C conversion.
2023-08-17 Created a test_data directory.
2023-08-17 Added a unit test for the thermistor r to c function.
2023-08-17 Deleted experimental subdirectory.
2023-08-17 Moved sample log file to data directory.
2023-08-17 Deleted jupyter notebook
2023-08-17 Removed the display filter functionality. Not useful due to phase shift.
2023-08-18 Created skeleton ui board.
2023-08-18 Created a skeleton display board (based on adc)
2023-08-19 Increased the size of the debug logger line buffer.
2023-08-19 More progress on the Display board.
2023-08-19 Fixed unit test timing and refactored libraries.
2023-08-20 Tweaked platform io.
2023-08-20 Renamed io.h to gpio_pins.h.
2023-08-21 Simplified the in/out gpio pin classes.
2023-08-21 Cleaned up gpio_pins.h
2023-08-21 Enabled i2c4 in cube_ide
2023-08-21 Added comments to main.cpp.
2023-08-21 Added LED signaling in the error handler.
2023-08-21 Added error handler unit test and renamed App_Error_Handler() to error_handler::Panic()
2023-08-21 Added a TODO
2023-08-21 Assigned codes to invocations of error_handler::Panic
2023-08-22 Added a .gitignore file to the jupyter notebooks directory.
2023-08-22 Renamed the interpolation notebook.
2023-08-22 Now performing per channel global interpolation to have consistent 1ms data points.
2023-08-22 Added a missing import.
2023-08-23 Added a notbook with a low pass filter example.
2023-08-23 Commented out the down sampling.
2023-08-24 Various data collector imporvements.
2023-08-26 Cleaned up the down sampling code.
2023-09-25 Added a skeleton of pyinstaller script.
2023-09-25 Tweaked the config file format.
2023-09-25 Fixed 'mrk' channel name.
2023-10-03 Added stm32loader to requirements.txt.
2023-10-06 Cloned io into heater card. Before renaming.
2023-10-06 Renamed clone of io into heater
2023-10-07 Updated requirements.
2023-10-07 Added to the monitor a dry_run flag.
2023-10-07 Created a skeleton Heater board from ADC.
2023-10-08 Created first monitor binary.
2023-10-08 Calibrated LC1 adc offset.
2023-10-08 Added a binary for the log processor.
2023-10-08 Added data collector binary
2023-10-08 Generated controller release firmware
2023-10-09 Added comment.
2023-10-09 Added to the flasher a --dry_run flag.
2023-10-10 Added peak detector simulator
2023-10-11 Work in spice sim.
2023-10-12 Added to the falsher a -f flag.
2023-10-12 Generated the data collector
2023-10-12 Tweaked the RMS circuit.
2023-10-13 More progress on the heater design.
2023-10-14 Heater schematic. Work in progress.
2023-10-21 Updated heater schematic.
2023-10-22 Updated the heater schematic.
2023-10-24 Updated controller's todo.
2023-10-28 Renamed custom board file. No semantic changhe.
2023-10-28 Added I2C1 definitions. Not used yet.
2023-10-29 Added a skeleton of i2c process.
2023-10-29 Added controller app note doc.
2023-10-29 Reformatted file. No semantic change.
2023-10-31 Added log data queue.
2023-10-31 Reformatted file path print.
2023-11-03 Updated heater shchematic (fixed +v rail labels)
2023-11-04 Updated controller todo.
2023-11-04 Commented out a data_queue logger message.
2023-11-04 Split the i2c read_reg into two I2c transactions.
2023-11-04 Updated ADC header comments. No semantic change.
2023-11-04 Refactored i2c handler to seperate setup from timer tick.
2023-11-05 I2C now runs on an rtos timer.
2023-11-05 Added serialization of I2C log packets.
2023-11-05 Made the graph updates smoother.
2023-11-05 Tweaked graphs labels and span.
2023-11-06 Updated heater schematic. No semantic change.
2023-11-06 Added to the monitoring 0.3sec buffering time to avoid flickering.
2023-11-06 Added a comment with Mac data link port.
2023-11-07 Changed the i2c timestamps to be samples at the beginning of each timer event for extra consistency.
2023-11-07 Removed commented out code. Updated controller's TODO.
2023-11-07 Commented out two log messages.
2023-11-07 Fixed the marker parsing.
2023-11-07 Adapted the log processor to the new log parser.
2023-11-07 Added an automatic detection of the I2C card.
2023-11-07 Switched platformio from my_genericSTM32H750VB to genericSTM32H750VB board.
2023-11-08 Renamed adc to adc_card.
2023-11-08 Renamed lib directory to pw_card, printer_link_card.
2023-11-08 Updated com port.
2023-11-08 Changed the channel id from a binary but to a three char string.
2023-11-08 Added to the log processor reporting of ignored channels.
2023-11-10 Changed the static timer to accept the period value in start() instead of in the constructor(). Also exposed the user provided value pvTimerID.
2023-11-10 Updated controllers TODOs.
2023-11-11 Simplify the StaticTask class and added the concept of Runnable.
2023-11-11 Added TimerCallback to allow timer dispatch to instances.
2023-11-11 Made the pw_card code a class.
2023-11-12 Added states as a preparation for scheduler based I2C hardware detection.
2023-11-12 Added PW Card hardware existance test.
2023-11-12 Added a TODO.
2023-11-13 Heater PCB layout in progress.
2023-11-13 Heater layout work in progress.
2023-11-13 More progress with the heatrer layout
2023-11-13 Heater layout work in progress. Passing all DRCs.
2023-11-13 Work in progress. Added silkscreen labels to the heater layout.
2023-11-14 Adjusted for JLCPCB upload.
2023-11-14 Changed the monitor to display pw1 watts instead of volts.
2023-11-15 Created a snapshot of the single rail heater before moving to a split rail design.
2023-11-15 Added commented out code.
2023-11-16 Updated the heater schematic. Using +/-5V dc/dc instead of a charge pump.
2023-11-17 Added series 0R resistors to the power supply rails.
2023-11-18 Cleaned up the sensing network.
2023-11-20 Added a critical section scope class. Not tested yet.
2023-11-20 Deleted the scopped critical section class.
2023-11-26 Updated heater shecmatic and sys config.
2023-11-26 Changed value of isense op amp serial resistor.
2023-11-26 Fixed the heater schematic title.
2023-11-28 Verified the footprints.
2023-11-28 Revert "Verified the footprints."
    This reverts commit 7ea96aa900b501c805e2681720e13a392d9a879a.
2023-11-28 Added comments to the heater schematic.
2023-11-28 Verified footprints and pinouts. (Recovered from a bad merge)
2023-11-28 Tweaked the vin indicator.
2023-11-28 Deleted an old version of the heater.
2023-11-28 Generated gerbers for heater
2023-12-01 Deleted old shell scripts.
2023-12-14 First step in adapting to the new markers format.
2023-12-15 Restructured the external reports. External data points now work.
2023-12-16 Cleaned up sys config
2023-12-16 Added display labels configurations.
2023-12-17 Increased the number of data buffers to avoid starvation.
2023-12-17 Fixed the handling of framing error.
2023-12-18 Tweaked the blue led blinking.
2023-12-19 Added plotting of recording range.
2023-12-19 Increased the speed of the blue LED during recording..
2023-12-19 Added to the log processor support for external report channels.
